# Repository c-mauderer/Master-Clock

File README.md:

# Master Clock

Note: Most of the documentation is written in English. But there is a short
German summary at the beginning.

## Summary (German)

Ziel des Projektes ist die Ansteuerung von Neben- beziehungsweise Tochteruhren ohne
zugehörige Mutteruhr. Als Energiequelle sollen Batterien verwendet werden.

Die Art von Nebenuhren, um die es hier geht, wurde z.B. häufig in Fabrikhallen
eingesetzt. Sehr häufig findet man sie z.B. mit Aufdruck von Siemens oder
ähnlichen Firmen. Die Nebenuhren sind so gebaut, dass der Minutenzeiger mit
einem Impuls um jeweils eine Minute weiterspringt. Dabei muss abwechselnd ein
positiver und ein negativer Spannungsimpuls angelegt werden. Üblicherweise
werden Uhren mit ±12 V oder ±24 V betrieben. Es scheint auch vereinzelte Modelle
mit höheren Spannungen zu geben.

Die Funktionsweise der Uhren wird von
[Rolf Süßbrich in einem ähnlichen Projekt](http://www.suessbrich.info/elek/ErsatzMutteruhr.html)
([archivierte Version](https://web.archive.org/web/20211020055925/http://www.suessbrich.info/elek/ErsatzMutteruhr.html))
gut erklärt. Die dort verwendete Schaltungsidee diente auch mir als Grundlage.
Allerdings habe ich zur Erzeugung des Minutenimpulses ein Mikrocontroller
eingesetzt, da dieser die Aufgabe stromsparender erledigen sollte, als
klassische CMOS-Bausteine. Statt am Eingang mit 10 Batterien für die 12V zu
arbeiten, wurde ein kleiner Step-Up-Regler aufgebaut, der auch für 24V Uhren
geeignet ist. Bei der Endstufe wurde die Idee aufgegriffen, einen
Operationsverstärker zur Ansteuerung zu verwenden.

### Useage (German)

Am Eingang der Platine kann eine Spannung von ca. 3 bis 10 V angelegt werden.
Höhere Spannungen führen dabei voraussichtlich zu niedrigeren Strömen beim
Schaltreglerteil. Der Prozessor wird über einen Linearregler versorgt und hat
daher einen konstante Stromaufnahme (und damit eine steigende Energieaufnahme
bei steigender Spannung). Der Schaltreglerteil sollte allerdings beim
Energiebudget überwiegen.

Am Ausgang wird der Motor der Uhr angeschlossen. Die Polarität ist dabei nicht
relevant.

Je nach Uhrwerk kann es sein, dass der Ausgangskondensator (C5) eventuell etwas
größer oder kleiner dimensioniert werden kann. Er sollte jedoch immer kleiner
als C4 sein. Kleinere Kondensatoren führen zu einer geringeren Stromaufnahme und
damit zu einer längeren Batterielebensdauer. Größere Kondensatoren liefern mehr
Energie für jeden Schritt des Zeigers.

Die Tasten werden einmal pro Sekunde ausgewertet, müssen also etwas länger
gedrückt werden. Die beiden Tasten haben folgende Funktionen:

PAUSE: Setzt die Minutensprünge aus. Während der Pausenzeit blinkt die LED jede
Sekunde kurz auf um den Zustand anzuzeigen. Kann mit STEP fortgesetzt
werden.

STEP: Wird die Taste mindestens eine Sekunde lang gedrückt, wird nach 5 Sekunden
ein Minutensprung ausgelöst. Ab diesem Zeitpunkt wird dann die nächste Minute
gezählt. Die 5 Sekunden sind notwendig, um dem Ausgangskondensator genügend Zeit
zum Laden zu geben. Ein erkannter Tastendruck wird mit einem kurzen Blinken der
LED bestätigt.

Beim Einlegen der Batterien oder manuellem Verstellen der Zeiger kann es
vorkommen, dass der erste Sprung ausbleibt. Das hängt von der Position des
Motors ab.

## Summary

The aim of the project is to control so called slave clocks without an
associated master clock. Batteries are to be used as the energy source.

The type of slave clocks in question were often used for example in factory
halls. They are very often found with the imprint of Siemens or similar
companies. The slave clocks are designed so that the minute hand advances by one
minute at a time with each electric pulse. A positive and a negative voltage
pulse must be applied alternately. Clocks are usually operated with ±12 V or ±24
V. There also appear to be a few models with higher voltages.

The operation of the clocks is well explained in German by
[Rolf Süßbrich in a similar project](http://www.suessbrich.info/elek/ErsatzMutteruhr.html)
([archived Version](https://web.archive.org/web/20211020055925/http://www.suessbrich.info/elek/ErsatzMutteruhr.html)).
I used the same basic idea as that project. However, I used a microcontroller to
generate the minute pulse, as this should do the job more energy-efficiently
than classic CMOS components. Instead of working with 10 batteries for the 12 V
input, a small step-up regulator was built, which is also suitable for 24 V
clocks. For the output stage, the idea of using an operational amplifier was
taken up.

### Useage Instructions

A voltage of approx. 3 to 10 V can be applied to the input of the circuit board.
Higher voltages are likely to lead to lower currents in the switching regulator
section. The processor is supplied via a linear regulator and therefore has a
constant current consumption (and thus an increasing energy consumption with
increasing voltage). However, the switching regulator part should predominate in
the energy budget.

The motor of the clock is connected to the output. The polarity is not relevant.

Depending on the movement, the output capacitor (C5) may be slightly larger or
smaller. However, it should always be smaller than C4. Smaller capacitors result
in lower current consumption and therefore a longer battery life. Larger
capacitors supply more energy for each step of the minute hand.

The buttons are analysed once per second, so they must be pressed a little
longer than that. The two buttons have the following functions:

PAUSE: Pauses the minute jumps. During the pause time, the LED flashes briefly
every second to indicate the status. Can be continued with STEP.

STEP: If the button is pressed for at least one second, a minute jump is
triggered after 5 seconds. The next minute is then counted from this point. The
5 seconds are necessary to give the output capacitor enough time to charge. A
recognised button press is confirmed by the LED flashing briefly.

When inserting the batteries or manually adjusting the hands, the first jump may
not occur. This depends on the initial position of the motor.

## Long Story

This chapter contains a bit more details of the development process.

The whole story started with a visitor at our local Repair Cafe (a event where
people can bring broken stuff and where volunteers help with tools and knowledge
to repair the things). The visitor had two slave clocks that have been left over
after a renovation in his company and that he was allowed to take with him. This
type of clocks only work with a controller. So he wasn't able to use them.

The clocks picked my interest and therefore I analyzed them a bit more. I found
out that they need a alternating pulse of (in that case) ±24 V per Minute. I
promised that we will find a way to use the clocks but that it will need some
time.

After some research at home, I found out that the type of clocks are quite
common in bigger companies. There are controllers commercially available that
cost something around 100 Euro and usually need quite a bit of energy.

My first idea was to just put together some modules (step up converter, small
controller board, motor controller) and create a quick and dirty version of
these controllers. This not very optimized variant would have required a plug-in
power supply quite similar to the commercially available versions but would have
been only a fraction of the costs (around 15 to 20 Euro should be possible).

The big disadvantage was the plug-in power supply. The visitor would prefer, if
he could use batteries instead of that. That's why I threw this idea over board
and restarted from scratch. During my search for inspiration, I stumbled upon a
project from Rolf Süßbrich (see Summary for a link) that used a quite simple
approach. Instead of a full motor driver, this project generates a simple
rectangular signal with 0 V and +12 V levels. The trick to generate the negative
pulse is to connect a capacitor in series with the clock motor and drive the
positive side of the capacitor to +12 V or 0 V.

My problem with the circuit was: It uses a total of 10 batteries for the supply
to generate the 12 V. I have some experience with switching regulators so I
decided that it should be possible to do the same with a low power step up
converter.

### Simulation

I searched for some low power step-up converters. The LT8330 seemed to be a good
fit. So I started with a simulation. The first approach was to simulate the
complete circuit with a general purpose OPV (OP292) as the output driver. I
later replaced that OPV with a different one.

For the clock motor, I had a measurement of about 2 kOhm coil resistance and I
estimated the inductance to be something around 0.1 H based on the coil
geometry. That's a very rough estimate but it should be good enough for the
simulation.

So the first draft of the simulation looked like follows:

The simulation of the complete schematic took a long time (most part of a day
for a bit more than 200ms). So I split it up and simulated the DC/DC and OPV
part separately.

#### DC/DC part

For the DC/DC converter the following schematic has been used:

I added a source that integrates the used energy and displays it as an
equivalent voltage. 1 V equals to 1 Wh.

As a result of the simulation, the DC/DC converter should need about

    (1.31 µWh - 1.04 µWh) / (0.9 s - 0.2 s) = 0.39 µW

#### OPV and clock part

During the simulation of the OPV and clock part, I noted that the OP292 is not
an ideal candidate. Based on availability, existing simulation models (in
LTSpice) and datasheets, I decided to replace it with a LT1178 or a similar
OP193. Both are capable to drive a few mA on the output, can handle the voltage
range of 24V and have low quiescent currents.

So the following schematic has been simulated:

Which gave the following result:

That part of the schematic needs about 5 mWh in one hour so it's a consumption
of about 5 mW.

#### Battery estimate

Based on these numbers, I was able to estimate the necessary battery. The DC/DC
part can be neglected. So the main part are the 5 mW of the OPV + clock part.
According to Wikipedia, an AA alkaline battery should have a capacity between
1700 mAh and 2850 mAh. So as an estimate, 3000 mWh should be fine. With that,
the clock would work 3000 mWh / 5 mW = 600 hours = 25 days with a single cell.

Again according to Wikipedia, a C cell has up to 8000 mAh. So a single C cell
would reach for about 100 days. With three to four of that, a year should be
possible. That's good enough for the estimation.

### Real Hardware

The simulation results looked well enough. So I started to design a small
circuit board based on that using KiCAD. The schematic and layout can be found
in `Hardware/Master_Clock`. Outputs in PDF and Gerber files are available in
that folder too.

As a source for the minute pulse, I added a small ATTiny. The standby current at
1.8V is very low and even the operating current is tiny if the system is clocked
at 32kHz.

I wanted to be able to order the boards as cheap as possible. So I used a simple
2 layer technology. I decided to try Aisler for these simple boards. They came
out quite well and even with the Blitz service, they are reasonably priced.
Together with the parts, one board is about 27 Euro.

I haven't ordered a paste mask because I currently don't have a soldering oven.
So populating the boards is hand work.

### Software

The software is really simple. It just initializes all necessary hardware and
then sleeps. It wakes up the controller every second (using the PIT) and
switches the minute output to the other level.

### Tests and Measurements

#### Estimate Influence of C5

The first tests with the circuit worked really well. It worked more or less out
of the box. So I did some current consumption measurements. It's not simple to
measure currents that small. The multimeter that I used (a Owon HDS2102S) is not
really up to the job. The minimum current range is 200 mA with a resolution of
10 µA. I can connect it to the PC and (with some python scripting) I can get
about three measurements per second. The input capacitance of my circuit should
help a bit with the slow sampling rate. But despite that, with that range and
sampling rate, only a rough estimate is possible.

I started with the 470 µF capacitor for C5 that I originally planned. I supplied
the circuit from a USB power supply. With that, I recorded the following current
(orange; left axis) and calculated the consumption in As (green; right axis).

As a rough estimate from that graph, 2.6 As per hour are consumed (1.6 As at
19:00 and 2.9 As at 19:30). That's about 13 Ws per hour or 3.6 mW. That matches
astonishing well with the simulation results.

A lot of energy is put into the charging of the capacitor C5, regardless whether
that energy is needed to move the clock hands or not. So I tried to reduce the
capacitor to 100 µF. The clock still works well. The consumption dropped quite a
bit (note the different scale on the right axis).

Again a rough estimate from that graph leads to about 1.1 As per hour (0.2 As at
9:00 and 0.73 at 9:30). That's about 5.5 Ws per hour or 1.5 mW. The idle current
of about 150 to 200 µA (depending on the level of the minute output) is now a
relevant part of that consumption.

With an even smaller capacitor of 47 µF, the clock hands can't move any more.
A 47 µF parallel to a 22 µF works. So the 100 µF is already the lower limit that
should be useable. Assuming that the capacitor will age over time, most likely a
150 µF to 220 µF is a better choice.

#### Detailed Analysis

Especially with smaller capacitors for C5, the standby current is quite
relevant. Therefore I decided to take a more detailed look at what is using the
energy. Time to use a better meter. So I switched to a bench top meter with 5.5
digits at 5 readings per second measuring speed or 4.5 digits at 20 or 123
readings per second.

I decided to use a 220 µF capacitor for C5, because that's most likely the one
I'll later use. Beneath that, I switched to a laboratory power supply.

With 5 V supply, the current peaks to over 20 mA which would mean that I have to
use the 200 mA range. In that range, the resolution of the meter isn't
satisfactory any more at higher reading rates. Luckily, the high currents are
used for charging the capacitors. So the switching regulator is involved. By
just increasing the voltage to 10 V, I can avoid the currents over 20 mA and
therefore stick to the smaller range.

A recording with the length of a few minutes is shown here:

At the first minute pulse at about 49s, 0.0029 As or 29 mWs have been used. At
the third minute pules at about 169s, 0.0253 As or 253 mWs have been used. So
it's about 6.72 Ws per hour or 1.87 mW. A bit less then I expected for the 220
µF based on the earlier measurements. But I changed some other parameters
(higher voltage, better meter) so it's not unreasonable.

So what is using the energy? Let's take a look at the separate parts of the
schematic.

#### Part 1: Controller and Peripherals

I need the controller and it's peripherals for all other measurements for
generating the minute pulse. So I decided to check that one first.

The CPU is clocked with the 32 kHz oscillator. I power the controller with 1.8 V.
At these frequency and supply, the data sheet gives a typical consumption of 7
µA when active or 1.7 µA when idle (rated at 2V). The buttons have static
pull-ups and the LED is connected so that the idle (off) level of the pin is
low. So that shouldn't need any energy (except for some leakage current in the
capacitors parallel to the buttons). The oscillator is rated for 0.65 µA at 3.3V
or 0.38 µA at 1.2V. Let's assume the higher current. The LDO has a idle current
of something between 1.5 and 2.5 µA with no load. It is rated for 500 mA max so
the processor and peripherals should be basically no load. So the total
consumption should be below 10 µA.

That leaves the LED which is connected directly to the input voltage with a 2.2
kΩ resistor. At 10 V it should need about (10 V - 2 V) / 2.2 kΩ = 3.6 mA when
on. The LED is switched on only for very short flashes of 1 ms per minute. The
current should average to 60 nA which is a lot less than the rest of the
controller.

So much for theory. Now some measurements: I removed R13. With that, the whole
switching regulator part is disconnected. I recorded a [few minutes of
measurements](./Measurements/current_10V_controller_and_peripherals.svg) in the
2 mA range of my meter. As expected, there was a very low current most of the
time with a few peaks when the LED has been switched on. The LED pulses are a
bit too short. So the meter didn't capture them well. The graphics is not that
easy to evaluate in this case. So I switched to the statistics function of the
meter instead. The average current there is at 3.9 µA which is less than the 10
µA that I estimated and therefore it's a reasonable value for the controller.
The maximum value is at 0.91 mA. That's less than the LED needs. It's likely
that the capacitors on the board smoothed out the LED current a bit so it's
still a reasonable peak value.

In summary, the controller system behaves like expected.

#### Part 2: Step Up Regulator Without Load

The next part in the circuit is the step up regulator. It's possible that C4 or
the OPV U3 waste some energy. So I have to remove these for the next
measurement.

According to the data sheet, the LT8330 should need up to 10 µA in Sleep Mode
(not switching) or up to 1100 µA if it is in Active Mode (not switching). The
LT8330 will charge the output capacitor and then it should go into sleep mode as
long as the output voltage doesn't drop too far. Without a load, the capacitor
should keep the voltage for quite some time and therefore I would expect that
the LT8330 basically sleeps all the time.

The feedback network R2 and R4 will use some energy. The data sheet suggests
something in the range of 1 MΩ. During the design, I already decided that this
would use up to much energy and used a network with 10 MΩ and 750 kΩ instead.
The feedback pin current in in the range of 10 nA so that the network should
still work with an acceptable accuracy. Still, the network needs quite a bit of
current: I = 24 V / 10.75 MΩ = 2.2 µA. That's at 24 V. At the 10 V input, that
will be already about 6 µA.

So in summary, the input current should be around 16 µA at 10 V.

Again: Back to the measurement. R13 has to be assembled again. Unfortunately I
didn't plan to disconnect C4 or the OPV. So there is no simple resistor to
unsolder or a friendly trace that I could cut. Instead I have to unsolder C4 and
disconnect pin 7 of U3. Unfortunately, I soldered U3 too well so that I couldn't
just lift the pin. So I decided to cut off the trade right at the pin.

With that, the total supply current averaged to 16.3 µA, again with a few 1 mA
peaks of the LED. From part 1 I know that 3.9 µA are from the controller. So
the DC/DC converter needs about 12.4 µA. That matches well with the estimated
value.

#### Part 3: Buffer Capacitor C4

Now to one of the main suspects: The big buffer capacitor C4. During the initial
design, I neglected to check the leakage current of that capacitor. I just used
some default Panasonic capacitor with the part number ECA-1HM102B.

In the data sheet, the leakage current is given as I ≤ 0.01 CV or 3 µA after 2
minutes (whichever is greater). For my capacity, the CV value most likely is the
interesting one. C is the capacitance, V is the rated voltage. The formula is a
bit odd because usually Farad times Volt should give Coulomb and not Ampere. So
this is one of the formulas, where the manufacturer decided to skip the right
unit of the constant. The 0.01 should be 0.01 Hz. With that, I get the following
leakage current:

0.01 Hz * C * V = 0.01 Hz * 1000 µF * 50 V = 0.5 mA

At the 10 V rail, that would be even more (about 1.2 mA). That's huge compared
to all other parts that I had till now.

In a real world measurement, I only get 20 to 21 µA of the complete circuit
after a few minutes if C4 is connected again. Half of that is the base current
from Part 2, so the capacitor is a lot better then the data sheet tells. The big
risk here is, that the leakage current will increase quite heavily over time.

In theory, the big capacity of C4 might isn't even necessary. The motor of the
clock is a coil with a lot of windings and some series resistors. In my case, it
has about 4 kΩ. Even if I assume other clocks with a quarter of that, the
maximum current is 24 mA. Both OPVs that I selected can drive less than that
(LT1178 can sink or source 5 mA according to the datasheet summary; OP193
summary tells something about ±8 mA). The switching regulator should be well
capable of delivering up to 100 mA, so C4 shouldn't be necessary.

Result: C4 will be removed completely. A test with 3 V and 10 V input voltage
showed no problems with that at all.

#### Part 4: Operational Amplifier

Next part is the Operational Amplifier without a load. Only OP193 is analyzed.
That one works well so I haven't tested the alternative LT1178 at all.

For the test, only the clock is disconnected. With that the output capacitor C5
is open on one side and therefore shouldn't be relevant.

For the OP193, the data sheet lists a supply current of up to 30 µA per
amplifier at ±18 V supply voltage. I have a lower supply voltage of only 24 V
(which would be equivalent to a ±12 V supply voltage) and a chip variant with a
single amplifier. So my current should be below that.

Let's test that. From now on, the measurement has to check two situations: A low
and a high minute pulse. So I'll wait for a pulse, reset the average on the
meter, wait for about 30 to 50 seconds and check the reading.

For the one minute, that's 57.8 µA. For the other minute, it's 80.9 µA. I have
to reduce these values by the 12.4 µA of the controller and DC/DC regulator. But
these values are at the 10 V input. So the idle current is at least (57.8 -
12.4) * 10 V / 24 V = 19 µA for the one and 29 µA for the other minute. That's
in the expected range.

#### Analyzing the Amplifier Some More

Analog Devices provides a nice App Note
[AN-849](https://www.analog.com/media/en/technical-documentation/application-notes/AN-849.pdf),
why Op amps shouldn't be used as comparators like I did in my circuit. One Point
is that an Op amp might have an input protection circuit with some diodes, that
protects the input from a differential voltage higher than ± 0.6 V.

The Application note suggests to read the data sheet very carefully and check
for the following points:

- Low values of absolute maximum differential input voltage. The OP193 has a
  quite high value for that so that shouldn't be a problem.

- Graphs of bias current or input current vs. differential or common-mode
  voltage that show discontinuities or gross nonlinearity. The OP193 indeed has
  a Input Bias Current vs. Common-Mode Voltage that's quite heavily nonlinear.

- Evidence of phase-inversion. One evidence can be a limit of the common mode
  voltage. The OP193 indeed has a limit for that that is about 0.1 V above and
  1.5 V below the minimum or maximum supply voltage.

The alternative chip (LT1178) does look a bit better regarding that (especially
the second point). But it's most likely not ideal either.

Measurements on the negative input of OP193 shows a 15 mV jump if the positive
input is switched. That's not much but it's visible.

On the output, there is a rise time of 1.1 ms. But no sign of ringing. The same
is true for the fall time.

To avoid potential problems with the input, additional resistor are added at the
positive input:

- The MinPulse trace is cut and a 2.2 MΩ is used to close the trace again
- A 2.2 MΩ is connected to 1.8V on the OPV side of the MinPulse trace
- A 2.2 MΩ is connected to GND on the OPV side of the MinPulse trace

With these changes, the jump on the negative input is about 7 mV. It has an
absolute level of 610mW. The positive input is either 458 mV or 903 mV. The
current consumption is still (on the 10V side) at 58 µA in the one minute and 81
µA in the other minute.

#### Big Resistors

During measurements, I noted that the system is quite sensitive to touches. It's
very likely that the reason for this are the high values for some of the
resistors. To make the system more stable, I added the following changes:

* Reduce the divider R1 and R3 to two 2.2 MΩ instead of the 10 MΩ. This will
  increase the current on the 1.8V side (and due to the linear regulator) by
  only 0.3 µA and therefore isn't a problem.
* Change the divider for the LT8330 feedback voltage (R2 and R4). That one
  currently needs 2.4 µA. Alternative values are:
    * 4.7 MΩ and 330 kΩ. That will result in a voltage of 24.4 V.
    * 2.2 MΩ and 330 kΩ. That will result in a voltage of 12.3 V.

### Final Hardware

Wit the changes from above, I assembled the final hardware:

#### Final Tests

Some final tests to give an estimate how long a battery will last. For the
run time estimates, I assume that an AA battery has 3000 mWh and an C cell has
10000 mWh. These are roughly the same numbers like above. I only estimated a C
cell with a slightly lower capacity to be on the save side.

##### Recording current at 10 V

Power estimate:

* at 85 s: 0.007 As; at 445 s: 0.078 As
* → (0.071 As) / (6 min) * (10 V) = 1.97 mW
* 10 V is not a typical battery voltage. So no further estimate.

##### Recording current at 9 V

Power estimate:

* at 25 s: 0.002 As; at 385 s: 0.082 As
* → (0.080 As) / (6 min) * (9 V) = 2.00 mW
* 9 V would be 6 batteries.
  * AA would reach 3000 mWh * 6 / 2.00 mW ≈ 375 d
  * C would reach 10000 mWh * 6 / 2.00 mW ≈ 1250 d

##### Recording current at 7.5

Power estimate:

* at 50 s: 0.005 As; at 410 s: 0.105 As
* → (0.100 As) / (6 min) * (7.5 V) = 2.08 mW
* 7.5 V would be 5 batteries.
  * AA would reach 3000 mWh * 5 / 2.08 mW ≈ 300 d
  * C would reach 10000 mWh * 5 / 2.08 mW ≈ 1000 d

##### Recording current at 6 V

Power estimate:

* at 76 s: 0.012 As; at 436 s: 0.142 As
* → (0.130 As) / (6 min) * (6 V) = 2.17 mW
* 6 V would be 4 batteries.
  * AA would reach 3000 mWh * 4 / 2.17 mW ≈ 230 d
  * C would reach 10000 mWh * 4 / 2.17 mW ≈ 770 d

##### Recording current at 4.5 V

Power estimate:

* at 65 s: 0.014 As; at 425 s: 0.206 As
* → (0.192 As) / (6 min) * (4.5V) = 2.40 mW
* 4.5 V would be 3 batteries.
  * AA would reach 3000 mWh * 3 / 2.40 mW ≈ 160 d
  * C would reach 10000 mWh * 3 / 2.40 mW ≈ 520 d

##### Recording current at 3.0 V

Power estimate:

* at 55 s: 0.019 As; at 415 s: 0.328 As
* → (0.309 As) / (6 min) * (3V) = 2.58 mW
* 3 V would be 2 batteries.
  * AA would reach 3000 mWh * 2 / 2.58 mW ≈ 100 d
  * C would reach 10000 mWh * 2 / 2.58 mW ≈ 320 d

#### Things To Do

* There are some minor bugs especially in the marking of the first PCB. These
  are documented in a README in the project folder.
* Add photos.

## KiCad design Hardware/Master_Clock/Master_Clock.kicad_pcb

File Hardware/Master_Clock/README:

# Open Bugs

- Missing marking for + and - on the supply input
- Missing marking for the negative terminal of the capacitors
- R7 and C11 are marked incorrectly on the silk screen
- Value of Output capacitor can be reduced.
- Pads of the electrolytic capacitors could be slightly larger
- C4 can be removed.
- Add a 2.2 MOhm in the MinPulse line and add a voltage divider with two 2.2
  MOhm between GND and 1.8 V on that line on the OPV side.
- Reduce R1 and R3 to 2.2 MOhm
- Change the divider for the LT8330 feedback voltage (R2 and R4). That one
  currently needs 2.4 µA. Alternative values are:
    * 4.7 MΩ and 330 kΩ. That will result in a voltage of 24.4 V.
    * 2.2 MΩ and 330 kΩ. That will result in a voltage of 12.3 V.

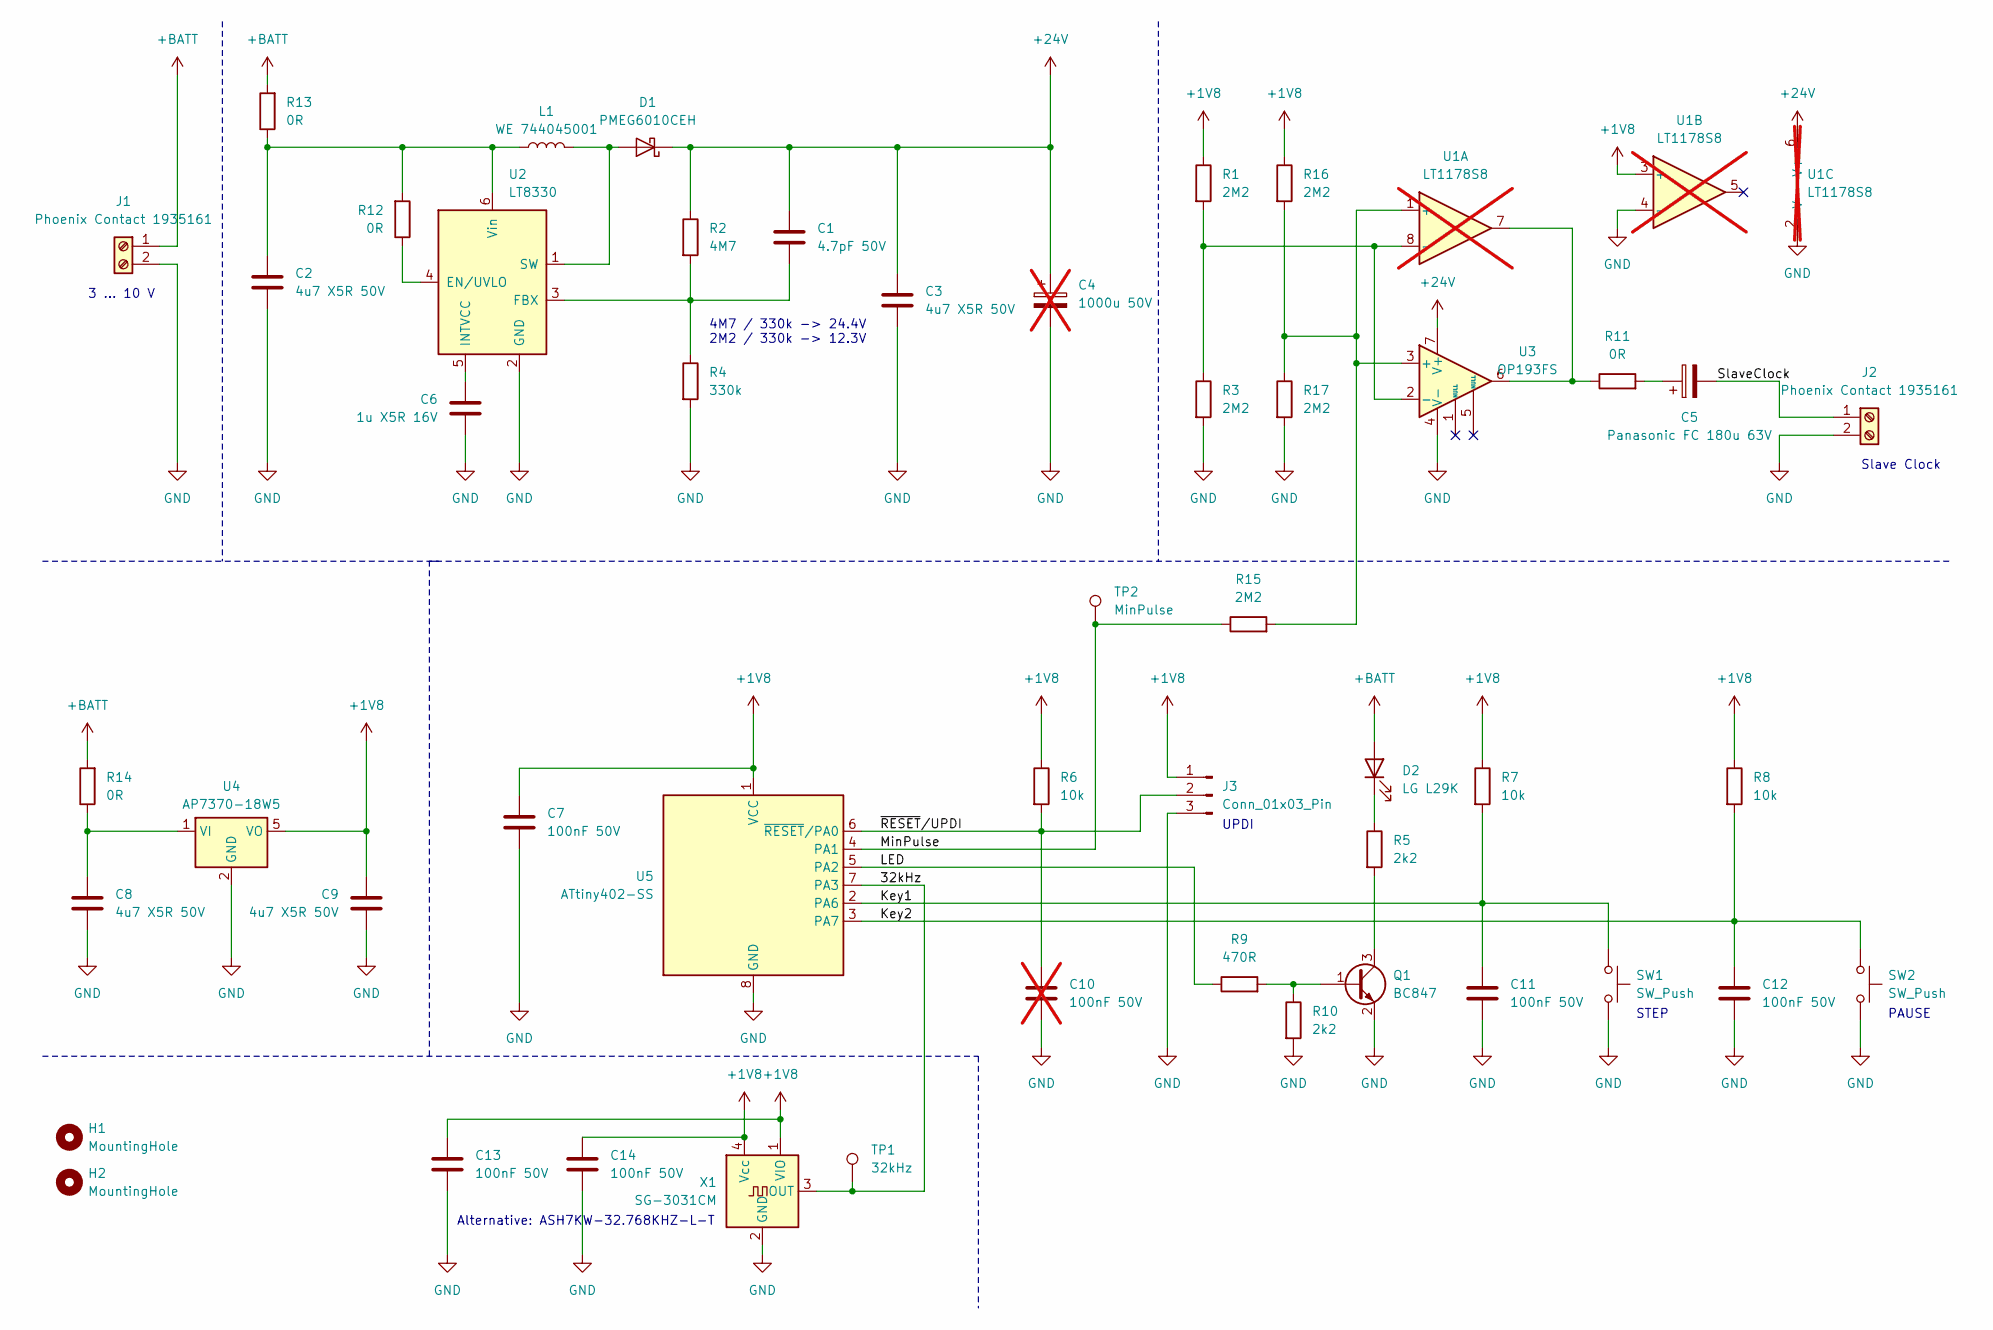
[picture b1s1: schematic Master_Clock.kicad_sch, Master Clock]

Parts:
C1: 4.7pF 50V; C_0603_1608Metric_Pad1.08x0.95mm_HandSolder
C2, C3, C8, C9: 4u7 X5R 50V; C_0805_2012Metric_Pad1.18x1.45mm_HandSolder
C4: 1000u 50V; C_Radial_D12.5mm_H25.0mm_P5.00mm; not fitted
C5: Panasonic FC 180u 63V; C_Radial_D12.5mm_H25.0mm_P5.00mm
C6: 1u X5R 16V; C_0603_1608Metric_Pad1.08x0.95mm_HandSolder
C7, C11, C12, C13, C14: 100nF 50V; C_0603_1608Metric_Pad1.08x0.95mm_HandSolder
C10: 100nF 50V; C_0603_1608Metric_Pad1.08x0.95mm_HandSolder; not fitted
D1: PMEG6010CEH; D_SOD-123F
D2: LG L29K; LED_0603_1608Metric_Pad1.05x0.95mm_HandSolder
H1, H2: MountingHole; MountingHole_3.2mm_M3_ISO7380_Pad
J1, J2: Phoenix Contact 1935161; TerminalBlock_Phoenix_PT-1,5-2-5.0-H_1x02_P5.00mm_Horizontal
J3: Conn_01x03_Pin; PinHeader_1x03_P2.54mm_Vertical
L1: WE 744045001; L_1812_4532Metric_Pad1.30x3.40mm_HandSolder
Q1: BC847; SOT-23
R1, R3, R15, R16, R17: 2M2; R_0603_1608Metric_Pad0.98x0.95mm_HandSolder
R2: 4M7; R_0603_1608Metric_Pad0.98x0.95mm_HandSolder
R4: 330k; R_0603_1608Metric_Pad0.98x0.95mm_HandSolder
R5, R10: 2k2; R_0603_1608Metric_Pad0.98x0.95mm_HandSolder
R6, R7, R8: 10k; R_0603_1608Metric_Pad0.98x0.95mm_HandSolder
R9: 470R; R_0603_1608Metric_Pad0.98x0.95mm_HandSolder
R11, R12, R13, R14: 0R; R_0603_1608Metric_Pad0.98x0.95mm_HandSolder
SW1, SW2: SW_Push; SW_PUSH_6mm
TP1: 32kHz; TestPoint_Pad_D1.0mm
TP2: MinPulse; TestPoint_Pad_D1.0mm
U1: LT1178S8; SOIC-8_3.9x4.9mm_P1.27mm; not fitted
U2: LT8330; TSOT-23-6_HandSoldering
U3: OP193FS; SOIC-8_3.9x4.9mm_P1.27mm
U4: AP7370-18W5; SOT-23-5
U5: ATtiny402-SS; SOIC-8_3.9x4.9mm_P1.27mm
X1: SG-3031CM; Oscillator_SMD_SeikoEpson_SG3030CM

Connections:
+1V8: C7.1, C9.1, C13.1, C14.1, J3.1, R1.1, R6.1, R7.1, R8.1, R16.1, U1.3 (+), U4.5 (VO), U5.1 (VCC), X1.1 (VIO), X1.4 (Vcc)
+24V: C1.1, C3.1, C4.1, D1.1 (K), R2.1, U1.6 (V+), U3.7 (V+)
+BATT: D2.2 (A), J1.1, R13.2, R14.2
/32kHz: TP1.1, U5.7 (PA3), X1.3 (OUT)
/Key1: C11.1, R7.2, SW1.1, U5.2 (PA6)
/Key2: C12.1, R8.2, SW2.1, U5.3 (PA7)
/LED: R9.1, U5.5 (PA2)
/MinPulse: R15.1, TP2.1, U5.4 (PA1)
/SlaveClock: C5.2, J2.1
/~RESET/UPDI: C10.1, J3.2, R6.2, U5.6 (~RESET/PA0)
GND: C2.2, C3.2, C4.2, C6.2, C7.2, C8.2, C9.2, C10.2, C11.2, C12.2, C13.2, C14.2, J1.2, J2.2, J3.3, Q1.2 (E), R3.2, R4.2, R10.2, R17.2, SW1.2, SW2.2, U1.2 (V-), U1.4 (-), U2.2 (GND), U3.4 (V-), U4.2 (GND), U5.8 (GND), X1.2 (GND)
unnamed: C5.1, R11.2
unnamed: D1.2 (A), L1.2, U2.1 (SW)
unnamed: D2.1 (K), R5.1
unnamed: Q1.1 (B), R9.2, R10.1
unnamed: Q1.3 (C), R5.2
unnamed: R11.1, U1.7, U3.6
unnamed: R15.2, R16.2, R17.1, U1.1 (+), U3.3 (+)
unnamed: R1.2, R3.1, U1.8 (-), U3.2 (-)
unnamed: R12.1, U2.4 (EN/UVLO)
unnamed: C1.2, R2.2, R4.1, U2.3 (FBX)
unnamed: C6.1, U2.5 (INTVCC)
unnamed: C2.1, L1.1, R12.2, R13.1, U2.6 (Vin)
unnamed: C8.1, R14.1, U4.1 (VI)

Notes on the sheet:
UPDI
STEP
Alternative: ASH7KW-32.768KHZ-L-T
4M7 / 330k -> 24.4V 2M2 / 330k -> 12.3V
PAUSE
3 ... 10 V
Slave Clock

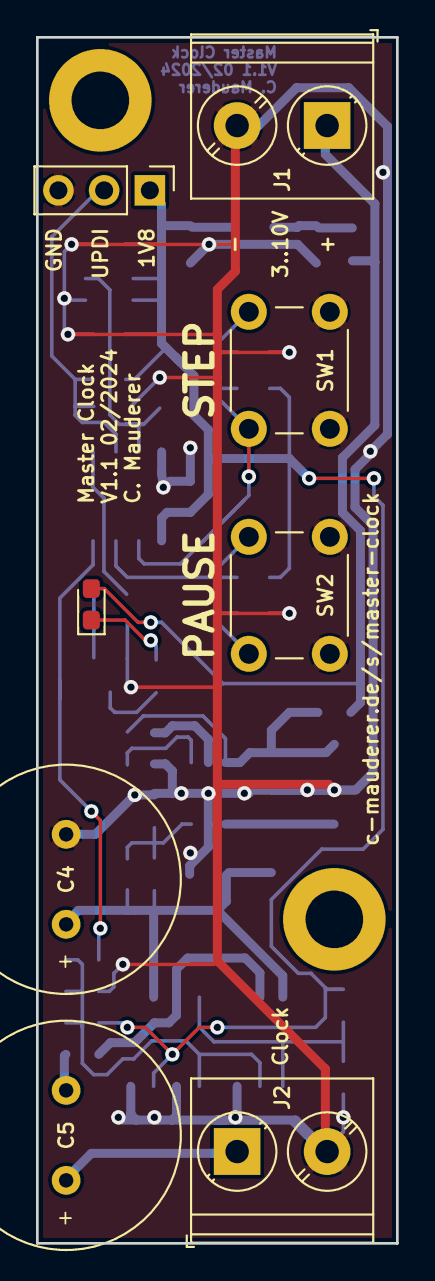
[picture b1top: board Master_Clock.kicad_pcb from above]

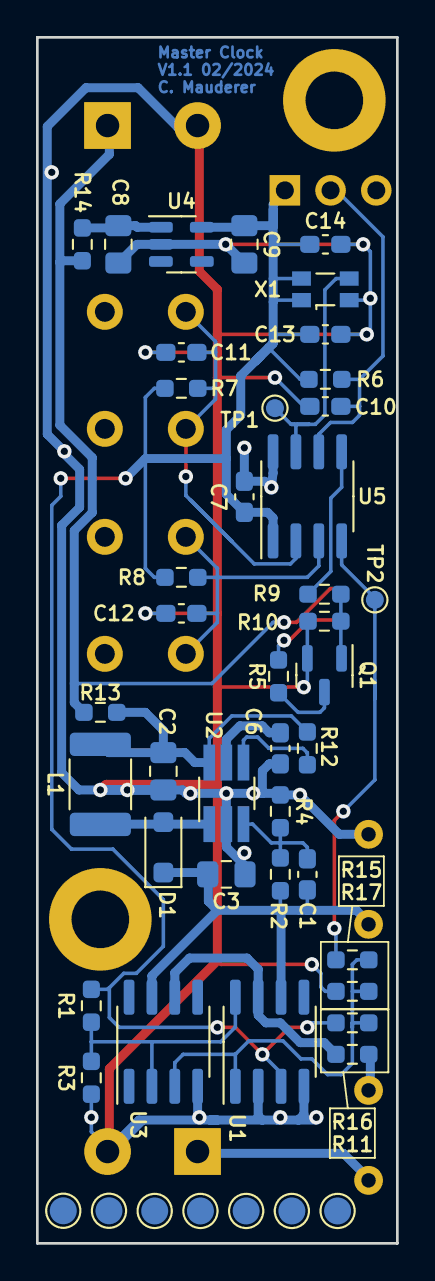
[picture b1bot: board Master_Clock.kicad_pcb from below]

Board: 2 copper layers, 20.0 x 67.0 mm, 50 parts (40 on the bottom side), 24 nets.

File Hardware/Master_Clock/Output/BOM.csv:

"Source:","/home/christian/aa/Projekte/Mutteruhr/Hardware/Master_Clock/Master_Clock.kicad_sch"
"Date:","Sa 17 Feb 2024 17:48:32 CET"
"Tool:","Eeschema 7.0.10"
"Generator:","/usr/share/kicad/plugins/bom_csv_grouped_by_value_with_fp.py"
"Component Count:","50"
"Ref","Qnty","Value","Cmp name","Footprint","Description","Vendor","DNP"
"C1","1","4.7pF 50V","C","Capacitor_SMD:C_0603_1608Metric_Pad1.08x0.95mm_HandSolder","Unpolarized capacitor","",""
"C2, C3, C8, C9","4","4u7 X5R 50V","C","Capacitor_SMD:C_0805_2012Metric_Pad1.18x1.45mm_HandSolder","Unpolarized capacitor","",""
"C4","1","1000u 50V","C_Polarized","Capacitor_THT:C_Radial_D12.5mm_H25.0mm_P5.00mm","Polarized capacitor","","DNP"
"C5","1","Panasonic FC 180u 63V","C_Polarized","Capacitor_THT:C_Radial_D12.5mm_H25.0mm_P5.00mm","Polarized capacitor","",""
"C6","1","1u X5R 16V","C","Capacitor_SMD:C_0603_1608Metric_Pad1.08x0.95mm_HandSolder","Unpolarized capacitor","",""
"C7, C11, C12, C13, C14","5","100nF 50V","C","Capacitor_SMD:C_0603_1608Metric_Pad1.08x0.95mm_HandSolder","Unpolarized capacitor","",""
"C10","1","100nF 50V","C","Capacitor_SMD:C_0603_1608Metric_Pad1.08x0.95mm_HandSolder","Unpolarized capacitor","","DNP"
"D1","1","PMEG6010CEH","PMEG6010CEH","Diode_SMD:D_SOD-123F","60V, 1A very low Vf MEGA Schottky barrier rectifier, SOD-123F","",""
"D2","1","LG L29K","LED","LED_SMD:LED_0603_1608Metric_Pad1.05x0.95mm_HandSolder","Light emitting diode","",""
"H1, H2","2","MountingHole","MountingHole","MountingHole:MountingHole_3.2mm_M3_ISO7380_Pad","Mounting Hole without connection","",""
"J1, J2","2","Phoenix Contact 1935161","Screw_Terminal_01x02","TerminalBlock_Phoenix:TerminalBlock_Phoenix_PT-1,5-2-5.0-H_1x02_P5.00mm_Horizontal","Generic screw terminal, single row, 01x02, script generated (kicad-library-utils/schlib/autogen/connector/)","",""
"J3","1","Conn_01x03_Pin","Conn_01x03_Pin","Connector_PinHeader_2.54mm:PinHeader_1x03_P2.54mm_Vertical","Generic connector, single row, 01x03, script generated","",""
"L1","1","WE 744045001","L","Inductor_SMD:L_1812_4532Metric_Pad1.30x3.40mm_HandSolder","Inductor","",""
"Q1","1","BC847","BC847","Package_TO_SOT_SMD:SOT-23","0.1A Ic, 45V Vce, NPN Transistor, SOT-23","",""
"R1, R3, R15, R16, R17","5","2M2","R","Resistor_SMD:R_0603_1608Metric_Pad0.98x0.95mm_HandSolder","Resistor","",""
"R2","1","4M7","R","Resistor_SMD:R_0603_1608Metric_Pad0.98x0.95mm_HandSolder","Resistor","",""
"R4","1","330k","R","Resistor_SMD:R_0603_1608Metric_Pad0.98x0.95mm_HandSolder","Resistor","",""
"R5, R10","2","2k2","R","Resistor_SMD:R_0603_1608Metric_Pad0.98x0.95mm_HandSolder","Resistor","",""
"R6, R7, R8","3","10k","R","Resistor_SMD:R_0603_1608Metric_Pad0.98x0.95mm_HandSolder","Resistor","",""
"R9","1","470R","R","Resistor_SMD:R_0603_1608Metric_Pad0.98x0.95mm_HandSolder","Resistor","",""
"R11, R12, R13, R14","4","0R","R","Resistor_SMD:R_0603_1608Metric_Pad0.98x0.95mm_HandSolder","Resistor","",""
"SW1, SW2","2","SW_Push","SW_Push","Button_Switch_THT:SW_PUSH_6mm","Push button switch, generic, two pins","",""
"TP1","1","32kHz","TestPoint","TestPoint:TestPoint_Pad_D1.0mm","test point","",""
"TP2","1","MinPulse","TestPoint","TestPoint:TestPoint_Pad_D1.0mm","test point","",""
"U1","1","LT1178S8","LT1178S8","Package_SO:SOIC-8_3.9x4.9mm_P1.27mm","17μA Max, Dual, Single Supply,Precision Op Amp, SOIC-8","","DNP"
"U2","1","LT8330","LT8330xS6","Package_TO_SOT_SMD:TSOT-23-6_HandSoldering","Low IQ Boost/SEPIC/Inverting Converter with 1A, 60V Switch, TSOT-23","",""
"U3","1","OP193FS","OP193","Package_SO:SOIC-8_3.9x4.9mm_P1.27mm","Precision, Micropower Single Operational Amplifier, SOIC-8/TSSOP-8","",""
"U4","1","AP7370-18W5","AP7370-18W5","Package_TO_SOT_SMD:SOT-23-5","200mA Low-Dropout Linear Regulator, 1.8V fixed output, SOT25","",""
"U5","1","ATtiny402-SS","ATtiny402-SS","Package_SO:SOIC-8_3.9x4.9mm_P1.27mm","20MHz, 4kB Flash, 256B SRAM, 128B EEPROM, SOIC-8","",""
"X1","1","SG-3031CM","SG-3030CM","Oscillator:Oscillator_SMD_SeikoEpson_SG3030CM","32.768kHz Crystal Oscillator (SPXO)","",""

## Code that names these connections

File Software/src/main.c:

/*
 * Copyright (c) 2024 Christian Mauderer <oss@c-mauderer.de>
 *
 * Permission is hereby granted, free of charge, to any person obtaining a copy
 * of this software and associated documentation files (the "Software"), to deal
 * in the Software without restriction, including without limitation the rights
 * to use, copy, modify, merge, publish, distribute, sublicense, and/or sell
 * copies of the Software, and to permit persons to whom the Software is
 * furnished to do so, subject to the following conditions:
 *
 * The above copyright notice and this permission notice shall be included in
 * all copies or substantial portions of the Software.
 *
 * THE SOFTWARE IS PROVIDED "AS IS", WITHOUT WARRANTY OF ANY KIND, EXPRESS OR
 * IMPLIED, INCLUDING BUT NOT LIMITED TO THE WARRANTIES OF MERCHANTABILITY,
 * FITNESS FOR A PARTICULAR PURPOSE AND NONINFRINGEMENT. IN NO EVENT SHALL THE
 * AUTHORS OR COPYRIGHT HOLDERS BE LIABLE FOR ANY CLAIM, DAMAGES OR OTHER
 * LIABILITY, WHETHER IN AN ACTION OF CONTRACT, TORT OR OTHERWISE, ARISING FROM,
 * OUT OF OR IN CONNECTION WITH THE SOFTWARE OR THE USE OR OTHER DEALINGS IN THE
 * SOFTWARE.
 */

#define F_CPU 32768ul

#include <avr/io.h>

#include <avr/cpufunc.h>
#include <avr/interrupt.h>
#include <avr/sleep.h>
#include <util/delay.h>

FUSES =
{
	/* Watchdog disabled */
	.WDTCFG = 0,
	/* Brown Out detection disabled */
	.BODCFG = 0,
	/* Default is 20MHz. This application wants 32kHz. So not relevant. */
	.OSCCFG = FUSE_OSCCFG_DEFAULT,
	/* Make sure that UPDI is active. Otherwise use defaults. */
	.SYSCFG0 = (FUSE_SYSCFG0_DEFAULT & ~FUSE_RSTPINCFG1) | FUSE_RSTPINCFG0,
	/* Default is 64ms. That's fine. */
	.SYSCFG1 = FUSE_SYSCFG1_DEFAULT,
	/* No difference between application and boot. 0 tells it's all boot. */
	.APPEND = 0,
	.BOOTEND = 0,
};

#define LED_MASK (1 << 2)
#define KEY_STEP_MASK (1 << 6)
#define KEY_PAUSE_MASK (1 << 7)

#define LED_ON do { PORTA.OUTSET = LED_MASK; } while(0)
#define LED_OFF do { PORTA.OUTCLR = LED_MASK; } while(0)
#define LED_TOGGLE do { PORTA.OUTTGL = LED_MASK; } while(0)

#define KEY_STEP_GET ((PORTA.IN & KEY_STEP_MASK) != 0)
#define KEY_PAUSE_GET ((PORTA.IN & KEY_PAUSE_MASK) != 0)

/*
 * Setup I/Os:
 *
 * - PA0: Reset/UPDI -> Other/Special: UPDI
 * - PA1: Minute Pulse Output -> TCA0:WO1 or GPIO out
 * - PA2: LED Output -> GPIO out
 * - PA3: 32kHz Input -> Other/Special: EXTCLK
 * - PA6: Key STEP -> GPIO in
 * - PA7: Key PAUSE -> GPIO in
 */
static void
io_init(void)
{
	PORTA.DIRSET = LED_MASK;
	LED_OFF;

	PORTA.DIRCLR = KEY_STEP_MASK | KEY_PAUSE_MASK;
}

/*
 * According to Data Sheet, the pin for EXTCLK is automatically configured if
 * any peripheral is requesting this clock. So this has only to switch to
 * external clock.
 */
static void
clock_init(void)
{
	/* Switch to external 32kHz clock */
	ccp_write_io((uint8_t *)&CLKCTRL.MCLKCTRLA, CLKCTRL_CLKSEL_EXTCLK_gc);

	/* Disable prescaler */
	ccp_write_io((uint8_t *)&CLKCTRL.MCLKCTRLB, 0);
}

/*
 * Enable power down mode for sleep. Only BOD, WDT and PIT are active.
 */
static void
standby_init(void)
{
	SLPCTRL.CTRLA = SLPCTRL_SMODE_PDOWN_gc;
}

/*
 * Use the RTC PIT to wake up once every second.
 */
static void
timer_init(void)
{
	RTC.CLKSEL = RTC_CLKSEL_EXTCLK_gc;
	RTC.PITINTCTRL = RTC_PI_bm;
	RTC.PITCTRLA = 0xE;
	RTC.PITCTRLA |= RTC_PITEN_bm;
}

/*
 * Clear flag. Count time. Optionally: Toggle pins.
 */
ISR(RTC_PIT_vect)
{
	RTC.PITINTFLAGS = RTC_PI_bm;
	/* FIXME */
}

int
main (void)
{
	clock_init();
	io_init();
	timer_init();
	standby_init();

	for(int i = 0; i < 6; ++i) {
		LED_TOGGLE;
		_delay_ms(200);
	}
	LED_OFF;

	while (1) {
		sleep_mode();
		LED_ON;
		_delay_ms(20);
		LED_OFF;
	}

	return 0;
}

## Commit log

2024-01-21 Idea and first draft
2024-01-21 Start schematic.
2024-01-21 Move to subdir
2024-01-21 HW V1.0-2023-12-28 - Fix mechanical drawing.
2024-01-21 First simulation results
2024-01-21 HW V1.0.
2024-01-21 Simulation for DCDC only.
2024-01-21 BOM and DigiKey numbers.
2024-01-21 Simulation of OPV only
2024-01-21 Create PCB and import AislerHQ rules.
2024-01-21 HW V1.0-2023-12-28 - Add 0R-resistors in supply.
2024-01-21 Finished Schematic.
2024-01-21 Add HW Readme with bugs
2024-01-21 Fix bug with pause
2024-01-21 Some basic useage instructions
2024-01-21 Get rid of "outside array bounds" warning
2024-01-21 PIT initialization
2024-01-21 DRC.
2024-01-21 Adapt calls for programming
2024-01-21 Implement logic for stepping clock
2024-01-21 Add some testpoints. Just in case...
2024-01-21 Frame for application
2024-01-21 Update BOM
2024-01-21 Dry code some initialization
2024-01-21 Remove remaining parts of EEPROM
2024-01-21 Faster start
2024-01-21 Add PDFs
2024-01-21 Add documentation
2024-01-21 Select external oscillator
2024-01-25 Better measurements using Siglent Meter
2024-01-25 plot.py: Options to parse different columns
2024-01-26 Try to extend to other formats
2024-01-26 Extend to other formats
2024-01-26 Add cursors
2024-01-27 Notes about further measurements
2024-03-27 Correct values for OP193
2024-03-27 Measure current of processor
2024-03-27 More measurements
2024-03-27 Ideas what maybe went wrong.
2024-03-27 Final measurements.
2024-03-27 Plans to change the resistors.
2024-03-27 Fotos of the clocks.
2024-03-27 List of Patches in HW 1.0.
2024-03-27 Update instruction.
2024-03-27 Software: Binaries of working version.
2024-03-27 Hardware 1.1
